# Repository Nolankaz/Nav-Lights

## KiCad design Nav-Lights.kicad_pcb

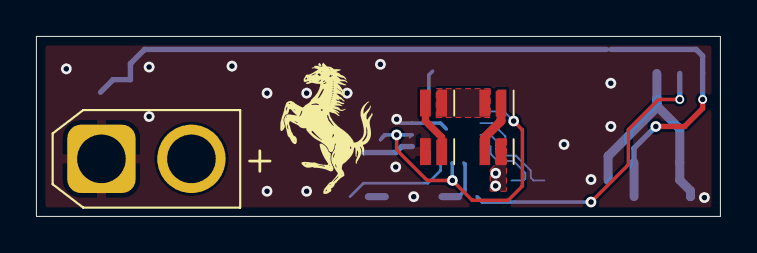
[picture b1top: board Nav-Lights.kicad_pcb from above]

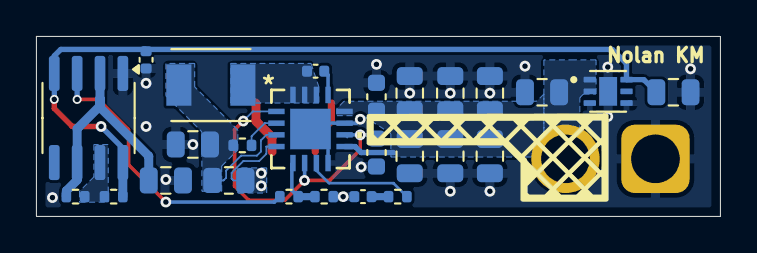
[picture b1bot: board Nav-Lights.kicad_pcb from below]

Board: 4 copper layers, 38.0 x 10.0 mm, 31 parts (26 on the bottom side), 18 nets.

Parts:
C1, C5, C11, C12, C13, C14, C15, C16: 10uF; C_0805_2012Metric
C3: 0.27uF; C_0805_2012Metric
C4: 0.1uF; C_0402_1005Metric
C6: 4.7uF; C_0805_2012Metric
C7: 47pF; C_0402_1005Metric
C8: 2.2uF; C_0603_1608Metric
C9: 22nf; C_0402_1005Metric
C10: 1uF; C_0603_1608Metric
D1, D2, D3, D4: LED; LED_0606 (M1616)
J1: Conn_01x02_Pin; AMASS_XT30U-M_1x02_P5.0mm_Vertical
L1: 22uH; IND_AMDLA4020S-220MT
R1: 100kOHm; R_0402_1005Metric
R2: 2490kOHm; R_0402_1005Metric
R3: 274kOhm; R_0402_1005Metric
R4: 10kO; R_0402_1005Metric
R5: 24mO; R_0805_2012Metric
R6, R7: R_US; R_0402_1005Metric
U1: LMC555CMMX; SOIC-8_3.9x4.9mm_P1.27mm
U2: TPS7B8133QWDRVRQ1; SON65P200X200X80-7N
U3: LT8374RUFM-WPBF; 05-08-1799_ADI

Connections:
+3V3: C4.1, C5.1, R1.1, U1.4 (R), U1.8 (VCC), U2.6 (OUT)
/Main/INTVCC: C8.1, U3.1 (SYNC/SPRD), U3.6 (CAP), U3.10 (INTVCC)
/Main/ISN: D1.2 (A), R5.2, U3.4 (ISN)
/Main/ISP: C6.2, L1.2, R3.1, R5.1, U3.3 (ISP)
/Main/THR: C3.1, R2.2, U1.2 (TR), U1.6 (THR)
/Main/VIN: C1.1, C10.1, C11.1, C12.1, C13.1, C14.1, C15.1, C16.1, J1.2, U2.1 (IN), U2.2 (EN), U3.9 (AVIN), U3.12 (VIN)
/Main/signal: R6.1, U1.3 (Q)
GND: C1.2, C3.2, C4.2, C5.2, C6.1, C7.2, C8.2, C10.2, C11.2, C12.2, C13.2, C14.2, C15.2, C16.2, D4.1 (K), J1.1, R7.2, U1.1 (GND), U2.3 (GND), U2.4 (GND), U2.7 (EXP), U3.8 (GND), U3.11 (GND), U3.17 (EPAD)
unnamed: C7.1, R4.2
unnamed: C9.2, L1.1, U3.14 (SW), U3.15 (SW), U3.16 (SW)
unnamed: D1.1 (K), D2.2 (A)
unnamed: D2.1 (K), D3.2 (A)
unnamed: D3.1 (K), D4.2 (A)
unnamed: R1.2, R2.1, U1.7 (DIS)
unnamed: C9.1, U3.13 (BST)
unnamed: R6.2, R7.1, U3.5 (CTRL)
unnamed: R3.2, U3.2 (FB)
unnamed: R4.1, U3.7 (VC)

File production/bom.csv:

Designator,Footprint,Quantity,Value,LCSC Part #
"C1, C11, C12, C13, C14, C15, C16, C5",0805,8,10uF,
C10,0603,1,1uF,
C3,0805,1,0.27uF,
C4,0402,1,0.1uF,
C6,0805,1,4.7uF,
C7,0402,1,47pF,
C8,0603,1,2.2uF,
C9,0402,1,22nf,
"D1, D2, D3, D4",LED_0606 (M1616),4,LED,
J1,AMASS_XT30U-M_1x02_P5.0mm_Vertical,1,Conn_01x02_Pin,
L1,IND_AMDLA4020S-220MT,1,22uH,
R1,0402,1,100kOHm,
R2,0402,1,2490kOHm,
R3,0402,1,274kOhm,
R4,0402,1,10kO,
R5,0805,1,24mO,
"R6, R7",0402,2,R_US,
U1,SOIC-8_3.9x4.9mm_P1.27mm,1,LMC555CMMX,
U2,SON65P200X200X80-7N,1,TPS7B8133QWDRVRQ1,
U3,05-08-1799_ADI,1,LT8374RUFM-WPBF,

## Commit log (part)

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2025-10-14 My first commit
2025-10-29 LEDboard
2025-10-29 newcircuit
2025-10-31 values
2025-11-01 valuesdone
2025-11-04 values, footprints, and part info complete
2025-11-12 imprv to layout
2025-11-13 Touching up layout
2025-11-13 Adding in HV stuff
2025-11-13 name change
2025-11-14 Finishing up layout
2025-12-17 starting cirular pcb
2025-12-28 optlayout
2026-01-06 new opt layout
2026-01-12 Layout w/ connector
2026-01-21 Adding in voltage divider for signal and layout and prod files
